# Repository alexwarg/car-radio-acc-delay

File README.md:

# Car Head-Unit ACC Timer

A small circuit and firmware based on an ATtiny85 that adds independent power-button control to a car head unit.

The device sits in-line with the vehicle's ACC (accessory/ignition) signal and gives you two extra capabilities:

- **ACC on:** the button can toggle the head unit off or back on while the ignition remains on.
- **ACC off:** the button turns the head unit on with an automatic 30-minute power-off timer, so you can keep listening after parking without draining the battery.

Power consumption in the off state is around 40 µA.

The project is available under the MIT license (see `LICENSE.txt`).

## Hardware

Minimal component count around an ATtiny85, designed for very low quiescent current.

The KiCad schematic and PCB layout are in `hardware/auto-acc-timer/`. A 3D-printable housing is in `hardware/auto-acc-timer/housing/`.

### MCU Pin Assignment

| Pin | Direction | Signal |
|-----|-----------|--------|
| PB1 | Input | Power button (active low, internal pull-up) |
| PB3 | Input | ACC input from vehicle |
| PB4 | Output | ACC output to head unit |
| PB0 | I²C SDA | Optional OLED display |
| PB2 | I²C SCL | Optional OLED display |

### J1 — Main Connector (1×6, 2.54 mm)

| Pin | Signal | Description |
|-----|--------|-------------|
| 1 | +12V | Vehicle power input |
| 2 | GND | Ground |
| 3 | ACC OUT | Switched ACC output to head unit |
| 4 | GND | Ground |
| 5 | BTN | Power button input |
| 6 | ACC IN | ACC input from vehicle ignition |

### J3 — ISP Programming Header / OLED Display (2×3, 2.54 mm)

| Pin | Signal | Description |
|-----|--------|-------------|
| 1 | MOSI (PB1) | SPI data in — shared with BTN net |
| 2 | VCC (3V3) | 3.3 V supply |
| 3 | SCK (PB2) | SPI clock / I²C SCL |
| 4 | MISO (PB0) | SPI data out / I²C SDA |
| 5 | RESET | MCU reset |
| 6 | GND | Ground |

J3 doubles as the OLED display connector. Connect an SSD1306 128×32 display using pins 2 (VCC), 3 (SCL), 4 (SDA), and 6 (GND).

## Operating Modes

| Condition | Short press | Long press |
|-----------|-------------|------------|
| ACC on, output on | Turn output off | — |
| ACC on, output off | Turn output on | — |
| ACC off, output off | Turn output on (starts 30 min timer) | — |
| ACC off, timer running | Cancel timer, turn output off | Reset timer to 30 min |

When the timer expires the output is cut automatically.

## Optional OLED Display

Compile with `USE_I2C=1` to enable an SSD1306 OLED (128×32) that shows the remaining time in `MM:SS` using a 7-segment font. A settings menu (long-press when idle) lets you adjust the power-off timer and the ACC-off delay; values are stored in EEPROM.

## Building

Requires `avr-g++` (C++20) and `avrdude`. The programmer is a Bus Pirate on `/dev/ttyUSB0`.

```sh
# Build firmware
make

# Flash firmware and EEPROM
make upload

# Regenerate font headers (requires tools/ttf2bmh.py)
make fonts
```

The build output lands in `.build/src/firmware.hex`.

## Software Overview

| File | Purpose |
|------|---------|
| `src/main.cc` | Application logic, pin setup, task loop |
| `src/timer.h` | 40-bit timer on USI/Timer1, ~1 kHz resolution at 8 MHz |
| `src/debounce.h` / `btn.h` | Debounce and button event detection (short/long/double press) |
| `src/task_list.h` | Cooperative task scheduler with idle-mode sleep |
| `src/i2c.h` | Non-blocking bit-bang I²C master driven by a flash-resident command program |
| `src/display.h` / `display.cc` | SSD1306 driver and font renderer |

See [`doc/i2c.md`](doc/i2c.md) for a detailed description of the I²C implementation.

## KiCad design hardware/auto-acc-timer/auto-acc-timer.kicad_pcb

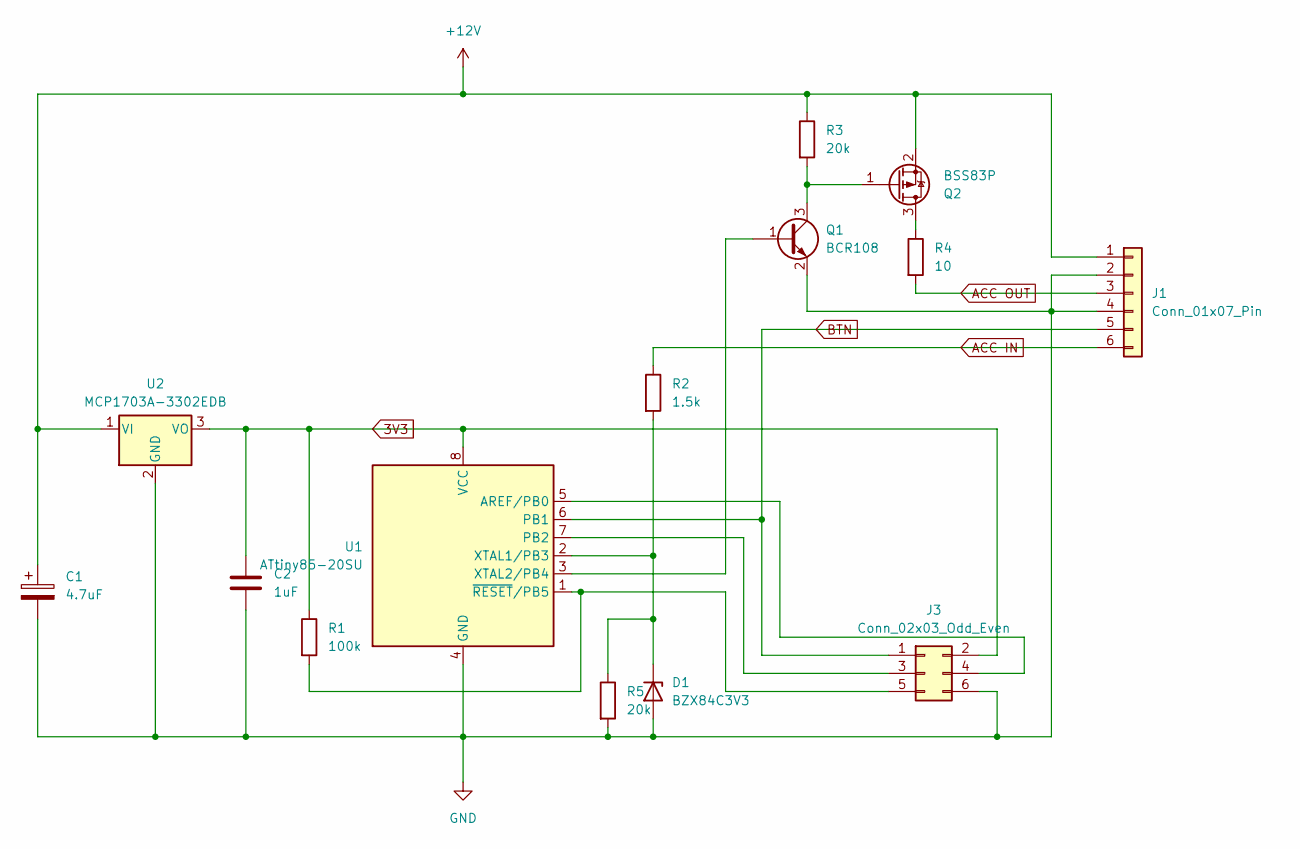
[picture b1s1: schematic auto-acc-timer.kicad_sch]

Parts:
C1: 4.7uF; CP_Elec_4x5.8
C2: 1uF; C_0805_2012Metric_Pad1.18x1.45mm_HandSolder
D1: BZX84C3V3; SOT-23
J1: Conn_01x07_Pin; PinHeader_1x06_P2.54mm_Vertical
J3: Conn_02x03_Odd_Even; PinHeader_2x03_P2.54mm_Vertical
Q1: BCR108; SOT-23
Q2: BSS83P; SOT-23
R1: 100k; R_0805_2012Metric_Pad1.20x1.40mm_HandSolder
R2: 1.5k; R_0805_2012Metric_Pad1.20x1.40mm_HandSolder
R3, R5: 20k; R_0805_2012Metric_Pad1.20x1.40mm_HandSolder
R4: 10; R_0805_2012Metric_Pad1.20x1.40mm_HandSolder
U1: ATtiny85-20SU; SOIC-8_5.3x5.3mm_P1.27mm
U2: MCP1703A-3302EDB; SOT-223-3_TabPin2

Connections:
3V3: C2.1, J3.2, R1.1, U1.8 (VCC), U2.3 (VO)
+12V: C1.1, J1.1, Q2.2 (S), R3.1, U2.1 (VI)
ACC IN: J1.6, R2.1
ACC OUT: J1.3, R4.2
BTN: J1.5, J3.1, U1.6 (PB1)
GND: C1.2, C2.2, D1.1 (A), J1.2, J1.4, J3.6, Q1.2 (E), R5.2, U1.4 (GND), U2.2 (GND)
unnamed: D1.3 (K), R2.2, R5.1, U1.2 (XTAL1/PB3)
unnamed: J3.3, U1.7 (PB2)
unnamed: J3.4, U1.5 (AREF/PB0)
unnamed: J3.5, R1.2, U1.1 (~RESET/PB5)
unnamed: Q1.1 (B), U1.3 (XTAL2/PB4)
unnamed: Q1.3 (C), Q2.1 (G), R3.2
unnamed: Q2.3 (D), R4.1

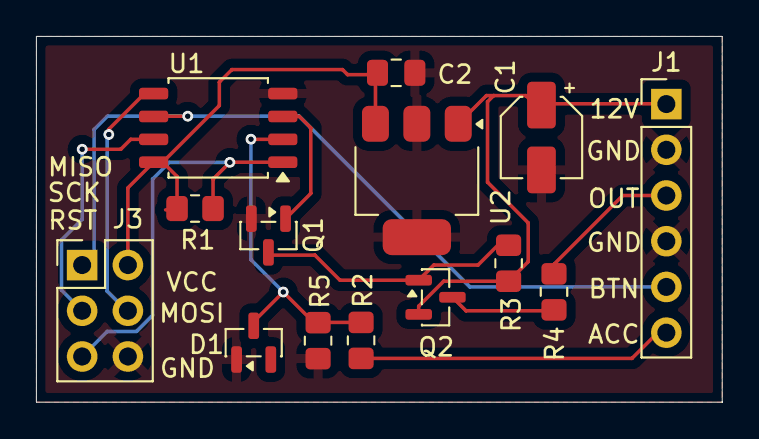
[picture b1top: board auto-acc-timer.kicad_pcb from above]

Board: 2 copper layers, 38.1 x 20.3 mm, 14 parts (0 on the bottom side), 13 nets.

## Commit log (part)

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2026-01-06 Initial version of CAR AUDIO DELAY
    This contains sime software for an AtTiny85 MCU and
    the hardware design.
2026-02-08 Fix wrong connection of Q2, move to KiCAD v 9
    The Q2 FET was connected the wrong way, fix that. and Move to KiCAD
    version9
2026-02-08 Some optimizations ...
2026-02-08 gitignore some stuff in hardware dir
2026-02-08 Actually enter sleep modes
    Call do_sleep() to actually enter the low-power modes of the MCU
2026-02-08 Add schematic PDF
2026-02-08 Optimize PCB layout
2026-02-08 Adapt IO pins to schematic
2026-02-08 Add README.md and schematic png
2026-02-08 Rev 2 Hardware
    Add capacitor 1uF at 3.3V rail
    Add resistor to pull RESET high
2026-02-08 Make sure to initialize debaounce after IOs
    Add init methd to Debounce class and use it after setting up
    the IOs. So we start with the correct initial state and do
    not detect a button release from before enabling the pullup.
2026-02-08 replace volatile globals by proper memory abbiers
    This shall allow for better optimization later
2026-02-08 remove useless debug flags
2026-02-08 Set timeout for auto-power-off to 30min
    The desired timer in real world is 30min so set this value.
2026-02-08 Do not use arduino framework
    The code is absed on AVR libc only
2026-02-08 Some refactoring into files
    Put helpers into separate header files, and into cxx namesapce.
2026-02-08 Add docs and license.
2026-02-09 Add housing CAD file
2026-02-09 Better code for timer etc
2026-02-09 Remove digispart env
2026-02-09 more refactoring of C++ helpers
2026-02-09 Add operator for simple 0 zero duration checking
2026-02-09 Add support for delayed ACC off
    delay the ACC output power off for 20 seconds after ACC input is going
    off.
2026-02-09 Add small notches in the housing
    The notches keep the PCB in place.
2026-02-10 Fix initialization bug in debounce
    Fix handling the initial state of the debouncer. We have to make sure
    the debouncer is initialized in stable state.
2026-02-12 Use uint32_t in cxx::ratio for better codegen
    The avr-gcc literally generates 64bit arithmetic shifts
    from divisions if int64_t is used as a denominator. This change helps to
    make sure the generated code is more efficient for our small
    microcontroller.
2026-02-12 Make default duration unsigned
    This resembles better what we actually do with durations an generates
    better asm code. This also makes sure we do the right kind of compare
    for gracefully dealing with wraparound timer counters and time points
    and durations that go across wraparounds.
    Fixes a bug in case of long timeouts where "now + timeout" triggers a
    wrap around. In this case the maximum timeout is half of the counter
2026-02-12 Improve debouncer code generation
    This change makes sure that there is no intermediate boolean data types
    created by the compiler and the asm code is more efficient this way.
2026-02-12 Add old-school Makefile for building
    Allow to use GNU Make for compiling the code. This allows for more
    flexible use of tool-chains that are not bundled with PlatformIO.
2026-02-21 timer.h: abstract from TCNT0
    allow simple use of other timer counter for timers
2026-02-21 Use Timer1 for timekeeping
    switch from Timer0 to Timer1 for general time keeping. This frees Timer0
    for other tasks, such as USI.
2026-05-06 Use C++ progmem abstration in i2c code
    Thsi moves from explicit use of pgm_* functions in i2c code to use
    if Pgm<> and Pgm_ptr<> and Gen_ptr<>. This also reduces code size
    in the i2c code.
2026-05-06 Add tons of std type_traits
2026-05-06 Migrate to std::ratio from cxx::ratio
2026-05-06 [aw11] pwr down delay to 0
2026-05-06 Add i2c data types for the master
2026-05-06 Enabled more warnings
2026-05-06 Unify i2c commands
    C_send_bytes and C_send_bytes_ram are equivalent if we use Gen_ptr<> as
    pointer type. Additionally also cleanup the C_send_bytes_ram_len cmd.
    The neew code uses a helper class and a well defined data type
    I2c_master::Send_buffer_data and I2c_master::Send_buffer...
2026-05-06 I2C: add check for busy queue
2026-05-06 Add cxx::void_t<>
2026-05-06 Remove accidental checking
2026-05-06 cleanup gcc options
    just use -Os instead of interleaved -O options
2026-05-06 remove unused code
2026-05-06 Run the CPU at 8MHz
    Adjust the prescaler for the CPU clock and the timer 1.
    CPU runs now at 8MHz, however timer 1 runs still at 8MHz / 8192,
    which is the same as 1MHz / 1024.
2026-05-06 Add C++ abstraction for progmem
2026-05-06 Add support for int = 8bit
2026-05-06 Tweak duration, to generate more efficient code
2026-05-06 Optimize eta calculation
2026-05-06 Add some (minimalistic) c++ std headers
    Add limited implementation for std C++ headers cstddef, type_traits,
    and utility.
2026-05-06 Add some literal suffix for durations
2026-05-06 Finish time display code in display.h
    * Some cleanup and reorg
    * Add clearing the space between numbers and at the end
2026-05-06 Add custom starter and finalizer for i2c commands
    This allows to handle the start and finish of i2c async cammd chains.
2026-05-06 Add font for SD1306
2026-05-06 Add I2C support and some SD1306 support
    Asnyc I2C framework for the ATTiny25/45/85.
    Add SD1306 support...
2026-05-06 Fix timer accuracy
    Originally the timer 1 tick is not 1us but actually 1ms / 1024.
    This change accurately pictures this in the duration ratios used for our
    data types. This also makes calculations in the seconds realm more
    efficient and precise, because the Timer::Hires_type >> 12 is now
    exactly one seconds.
2026-05-06 Add missing #pragma once to header
2026-05-06 Use out std C++ heaaders
2026-05-06 Add code to display a countdown when running on timer
2026-05-06 Add 16bit seconds type
2026-05-06 Add hooks in main.cc for i2c and display
2026-05-06 Simplify type definition
2026-05-06 More flexible status in Task_list::update
    This change allows to use either a callable object for getting the extra
    status for the Task::update functions, or to use a pointer to a status
    object that is passed as reference to the Task::update functions.
2026-05-06 Add "generated" pixmaps
2026-05-06 Add eeprom upload in one go
    Add some bitmap fot tools
2026-05-06 cxx::Pgm use uintptr_t
2026-05-06 Add OLED image generation to Makefile
2026-05-06 Add some symbols bitmaps
2026-05-06 Move time digit calculation to Display::time code
    Simply use the time in seconds for Display::time(sec) and calculate the
    digits for display internally. This does the calculation only after
    every second and not in each loop if the clock is ticking. The code size
    is also going down, as the new calculation takes less lib functions.
2026-05-06 cxx::Pgm: better array support
2026-05-06 Pass PINB as a pointer
    Pass a pointer to PINB as extra status to the task list. This way the
    loop will access the PINB directly whenever needed, instead of chaing
    the complete PINB value for the update functions.
2026-05-06 uploadeep target
2026-05-06 cxx::Pgm: improve array handling
    Make Pgm<> objects actually const internally, including the array
    version. This is done by cleverly unpacking a given native array into
    the internal one at compile time.
2026-05-06 Add common_type<> for cxx::duration
2026-05-06 cxx::Pgm: improve conversion handling
    Allow automatic conversion of a Pgm<T[]> array type to a Pgm_ptr<T>,
    just like the native array decay.
    Add conversion (automatic) from native pointer to Gen_ptr, and
    from convertible Pgm_ref<Pmg_ptr<>> objects.
2026-05-06 Optimize unused arguments
    Make sure unused arguments to update and wakeup functions of tasks are
    perfectly forwarded. This avoids costly dereferencing of potentially
    volatile state in those cases.
2026-05-06 Add button helper
    Add a cxx::Btn class on top of cxx::Debounce that supports double click
    and short click and long click as actions.
2026-05-06 Add std::conjunction to type_trais
2026-05-06 utility: add std::forward<>()
2026-05-06 main.cc: Use Task_list
    Make use of the task list template and reduce the clutter in the main
    loop of our program. This also removed a lot of ifdefs for i2c display
    support.
2026-05-06 Add Sleep_support class
    The sleep support class provides an API to setup MCU sleep and
    power-down modes, and to actually go to sleep.
2026-05-06 Update fonts (newly generated)
2026-05-06 TTF2BMF features
2026-05-06 Set SRCROOT earlier in the Makefile
2026-05-06 Move from cxx_a to cxx namespace
    We need to use a well-known namespace otherwise non-local template
    specializations become complicated.
    Add missing implementation for cxx::move().
2026-05-06 cxx_pgm.h: fix alays_inline attribute cleanup
    Put the always_inline attribute with a gnu: prefix and at the right
    position in the function declaration.
    Use %a<n> constraints to get the 'Z' register
2026-05-06 Add std::lcm function
    This function is constexpr least common multiple of the arguments.
2026-05-06 Display + i2c changes
    Improve i2c commands, add dynamic repeat byte command to i2c.
    Use a loop of prepared commands to show a clock on the display.
    Add other helper functions to blit pixmaps etc..
2026-05-06 Use Task_list init
    do no longer call individual init functions for taks, but use the
    Task_list::init function. This removes another i2c ifdef.
2026-05-06 Add tool to convert images into 1bit OLED
2026-05-06 Add Task_list template
    The Task_lis<...> template is a static list of different tasks that can
    be run in a run loop. the have and update(..) function a might_sleep()
    and a might_power_down() function run in a loop.
2026-05-06 Add some types ant time-type specific now()
    This change allows to programaticaly read the current time in different
    time formats depending on the required precision. And also allows to use
    the always under lock versions of the functions.
2026-05-06 Add and improve documentation
2026-05-06 Fix indentation
2026-05-06 Rework bitmap generators and fonts
    Replace pgm_array() function with Pgm(<array>) constructor.
    Generate Pgm() objects for fonts too and organize the font data into a
    per font structure with static constexpr data members for all the font
    details. Avoid using a big array of char descriptors in fonts, as this
    is more expensive to calculate the indexes and might create code
    overhead for accessing the data.
2026-05-06 Add _on state bit to Display and consolidate code
    Handle display state explicitely in Display::_on bit and consolidate all
    i2c and display related code to a single ifdef and the Display_task
    class. This also now switches the display off if ACC is on and no timer
    is running.
2026-05-06 Display changes
    Use vertical bitmaps and fonts. This allows for a simpler implementation
    of spacing in fonts. Switch the clock to a 7seg font.
2026-05-06 Add settings support
    Allow to change the timeouts via settings menu
2026-05-06 C++ <utility>: add integer_sequence
    Add integer_sequence and index_sequence templates. Those come in handy
    for unpacking constant arrays at compile time for example.
2026-05-06 Move task loop to task_list.h
    The task loop is now part of Task_list class. All relevant topics to be
    done in the loop are now implemented as tasks in main.cc.
    Also a bit of cleanup and resorting of main.cc and comments.
2026-05-06 Adapt makefile to new TTF2BMF
2026-05-06 Improve Debounce code
    This change adds available state bits to the Debounce state that
    can be used in derived classes. It also now provides protected state
    modifier functions state_del, state_add, and state_modify, as well as
    have_state functions.
2026-05-06 PGM array support (part 2)
2026-05-06 cxx::duration: add <= and < operators
2026-05-06 Optimize code gen for Pgm access
